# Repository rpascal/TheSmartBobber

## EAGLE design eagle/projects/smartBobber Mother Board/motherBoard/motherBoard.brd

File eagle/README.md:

# Set up Eagle

Once downloaded:
 - options
 - directories
 - Set up paths to what was pulled from git

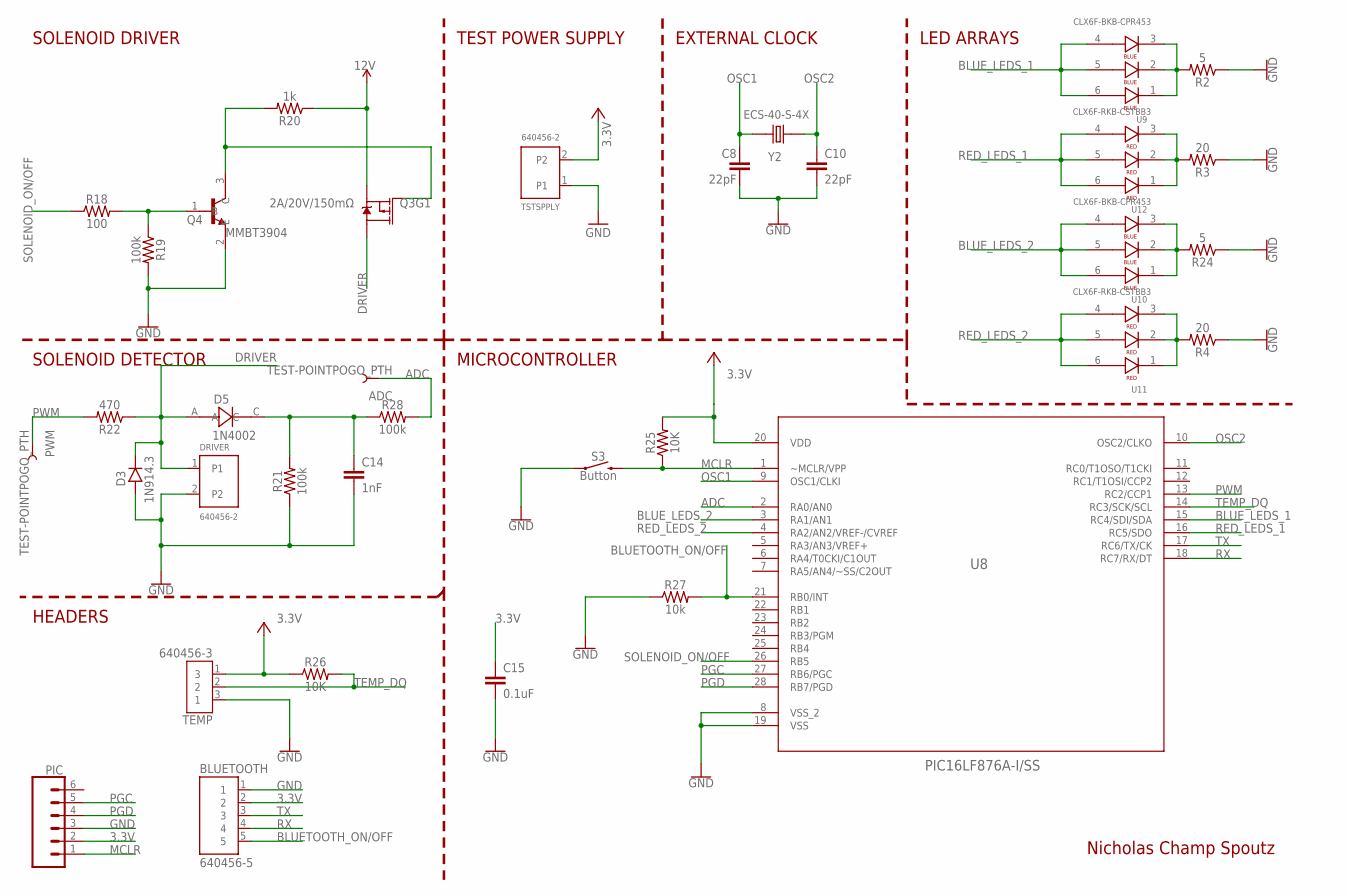
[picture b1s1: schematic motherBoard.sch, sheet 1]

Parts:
ADC: TEST-POINTPOGO_PTH; 1X01_NO_SILK
BLUETOOTH: 640456-5; TE_640456-5
C8, C10: 22pF; 0603
C14: 1nF; 0603
C15: 0.1uF; 0603
D3: 1N914.3; DO35-3
D5: 1N4002; DIOAD520W79L463D238
DRIVER: 640456-2; TE_640456-2
PIC: CONN_06SILK_FEMALE_PTH; 1X06
PWM: TEST-POINTPOGO_PTH; 1X01_NO_SILK
Q3: 2A/20V/150mΩ; SOT26
Q4: MMBT3904; SOT95P240X120-3N
R2, R24: 5; 0603
R3, R4: 20; 0603
R18: 100; 0603
R19, R21, R28: 100k; 0603
R20: 1k; 0603
R22: 470; 0603
R25, R26: 10K; 0603
R27: 10k; 0603
S3: Button; TACTILE_SWITCH_SMD_5.2MM
TEMP: 640456-3; CONN_640456-3
TSTSPPLY: 640456-2; TE_640456-2
U8: PIC16LF876A-I/SS; SOP254P785X200-28N
U9, U10: CLX6F-BKB-CPR453; SOJ100P350X290-6N
U11, U12: CLX6F-RKB-CSTBB3; SOJ100P350X290-6N
Y2: ECS-40-S-4X; XTAL_ECS-40-S-4X

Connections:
3.3V: BLUETOOTH.2, C15.1, PIC.2, R25.2, R26.1, TEMP.1 (3), TSTSPPLY.2, U8.20 (VDD); also elsewhere on the board
12V: Q3.S1 (S), R20.1; also elsewhere on the board
ADC: ADC.1, R28.2, U8.2 (RA0/AN0)
BLUETOOTH_ON/OFF: BLUETOOTH.5, R27.2, U8.21 (RB0/INT)
BLUE_LEDS_1: U8.15 (RC4/SDI/SDA), U9.4, U9.5, U9.6
BLUE_LEDS_2: U8.3 (RA1/AN1), U10.4, U10.5, U10.6
DRIVER: D3.C, D5.A, DRIVER.1, Q3.D1 (D), R22.1
GND: BLUETOOTH.1, C8.2, C10.2, C14.2, C15.2, D3.A, DRIVER.2, PIC.3, Q4.2 (E), R2.1, R3.1, R4.1, R19.2, R21.1, R24.1, R27.1, S3.1, TEMP.3 (1), TSTSPPLY.1, U8.8 (VSS_2), U8.19 (VSS); also elsewhere on the board
MCLR: PIC.1, R25.1, S3.3 (2), U8.1 (~MCLR/VPP)
unnamed: R2.2, U9.1, U9.2, U9.3
unnamed: C14.1, D5.C, R21.2, R28.1
unnamed: R3.2, U12.1, U12.2, U12.3
unnamed: R24.2, U10.1, U10.2, U10.3
unnamed: Q4.1 (B), R18.2, R19.1
unnamed: Q3.G1 (G), Q4.3 (C), R20.2
unnamed: R4.2, U11.1, U11.2, U11.3
OSC1: C8.1, U8.9 (OSC1/CLKI), Y2.1
OSC2: C10.1, U8.10 (OSC2/CLKO), Y2.2
PGC: PIC.5, U8.27 (RB6/PGC)
PGD: PIC.4, U8.28 (RB7/PGD)
PWM: PWM.1, R22.2, U8.13 (RC2/CCP1)
RED_LEDS_1: U8.16 (RC5/SDO), U12.4, U12.5, U12.6
RED_LEDS_2: U8.4 (RA2/AN2/VREF-/CVREF), U11.4, U11.5, U11.6
RX: BLUETOOTH.4, U8.18 (RC7/RX/DT)
SOLENOID_ON/OFF: R18.1, U8.26 (RB5)
TEMP_DQ: R26.2, TEMP.2, U8.14 (RC3/SCK/SCL)
TX: BLUETOOTH.3, U8.17 (RC6/TX/CK)

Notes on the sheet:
SOLENOID DRIVER
SOLENOID DETECTOR
HEADERS
TEST POWER SUPPLY
EXTERNAL CLOCK
LED ARRAYS
MICROCONTROLLER
Nicholas Champ Spoutz

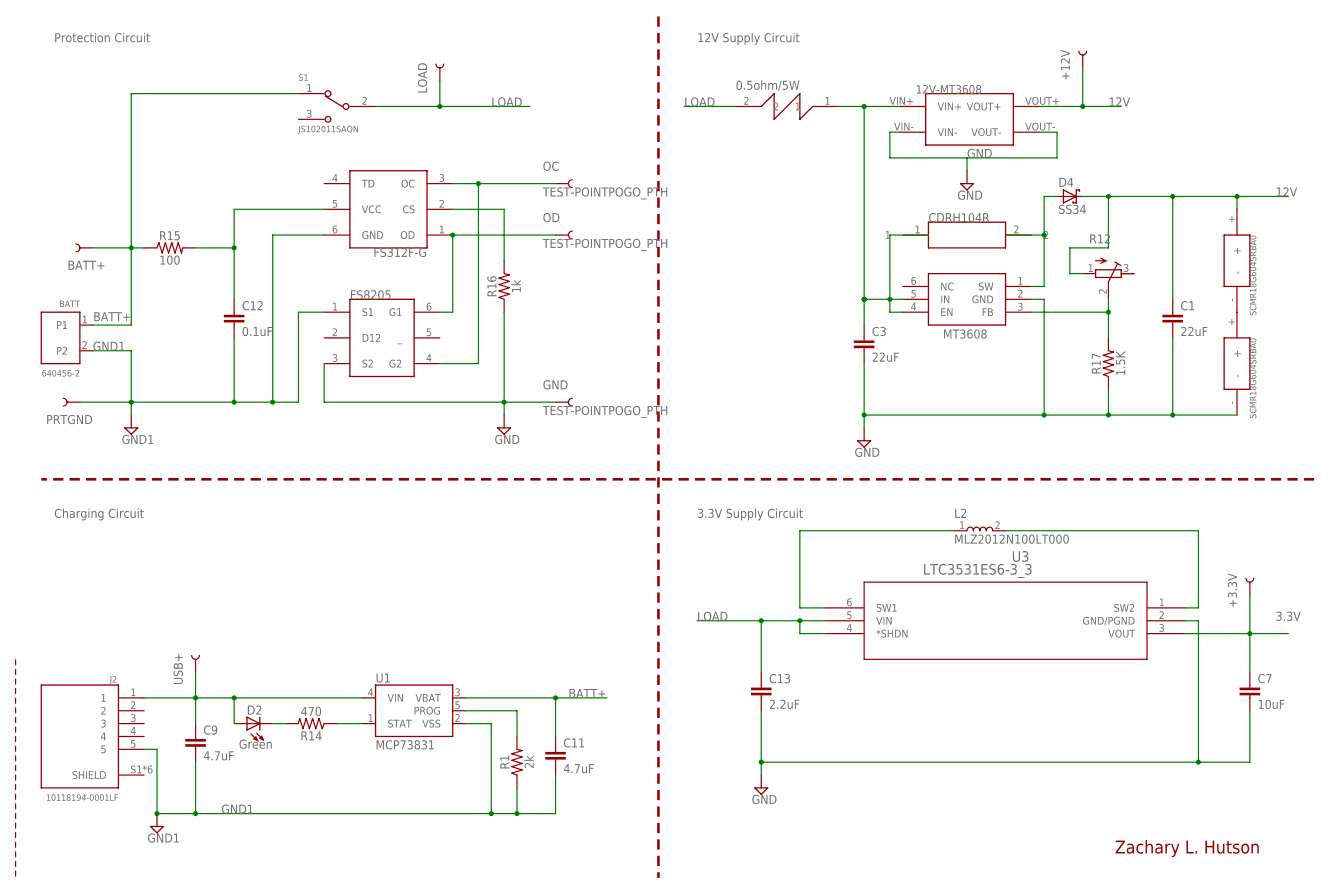
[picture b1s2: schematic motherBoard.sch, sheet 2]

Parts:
+3.3V, +12V: TEST-POINTPOGO_PTH; 1X01_NO_SILK
BATT: 640456-2; TE_640456-2
BATT+: TEST-POINTPOGO_PTH; 1X01_NO_SILK
C1: 22uF; 0805
C3: 22uF; 0603
C7: 10uF; 0603
C9, C11: 4.7uF; 0603
C12: 0.1uF; 0603
C13: 2.2uF; 0603
C16, C17: SCMR18G604SRBA0; SUPERCAP
D2: Green; LED-0603
D4: SS34; SMB
GND: TEST-POINTPOGO_PTH; 1X01_NO_SILK
J2: 10118194-0001LF; AMPHENOL_10118194-0001LF
L1: CDRH104R; 220-INDUCTOR
L2: MLZ2012N100LT000; INDC2012X125
LOAD: TEST-POINTPOGO_PTH; 1X01_NO_SILK
OC: TEST-POINTPOGO_PTH; 1X01_NO_SILK
OD: TEST-POINTPOGO_PTH; 1X01_NO_SILK
PRTGND: TEST-POINTPOGO_PTH; 1X01_NO_SILK
R1: 2k; 0603
R12: R-TRIMM3296P; RTRIM3296P
R14: 470; 0603
R15: 100; 0603
R16: 1k; 0603
R17: 1.5K; 0603
R30: WNER50FET; RESISTOR
S1: JS102011SAQN; SW_JS102011SAQN
U1: MCP73831; SOT23-5
U2: MT3608; SOT95P280X145-6N
U3: LTC3531ES6-3_3; TSOT-23_S6
U$1: 12V-BOARD; PERF_BOARD
U$3: FS312F-G; SOT-23-6
U$4: FS8205; SOT-23-6
USB+: TEST-POINTPOGO_PTH; 1X01_NO_SILK

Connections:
3.3V: +3.3V.1, C7.1, U3.3 (VOUT); also elsewhere on the board
12V: +12V.1, C1.1, C16.+, D4.C, R12.1 (E), U$1.VOUT+; also elsewhere on the board
BATT+: BATT.1, BATT+.1, C11.1, R15.1, S1.1, U1.3 (VBAT)
GND: C1.2, C3.2, C7.2, C13.2, C17.-, GND.1, R16.1, R17.1, U2.2 (GND), U3.2 (GND/PGND), U$1.VIN-, U$1.VOUT-, U$4.3 (S2); also elsewhere on the board
GND1: BATT.2, C9.2, C11.2, C12.2, J2.5, PRTGND.1, R1.1, U1.2 (VSS), U$3.6 (GND), U$4.1 (S1)
LOAD: C13.1, LOAD.1, R30.2, S1.2, U3.4 (*SHDN), U3.5 (VIN)
unnamed: D2.C, R14.2
unnamed: C3.1, L1.1, R30.1, U2.4 (EN), U2.5 (IN), U$1.VIN+
unnamed: R14.1, U1.1 (STAT)
unnamed: R1.2, U1.5 (PROG)
unnamed: R16.2, U$3.2 (CS)
unnamed: C9.1, D2.A, J2.1, U1.4 (VIN), USB+.1
unnamed: D4.A, L1.2, U2.1 (SW)
unnamed: R12.2 (S), R17.2, U2.3 (FB)
unnamed: L2.1, U3.6 (SW1)
unnamed: L2.2, U3.1 (SW2)
unnamed: OD.1, U$3.1 (OD), U$4.6 (G1)
unnamed: OC.1, U$3.3 (OC), U$4.4 (G2)
unnamed: C16.-, C17.+
unnamed: C12.1, R15.2, U$3.5 (VCC)

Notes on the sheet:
Charging Circuit
Protection Circuit
3.3V Supply Circuit
12V Supply Circuit
Zachary L. Hutson

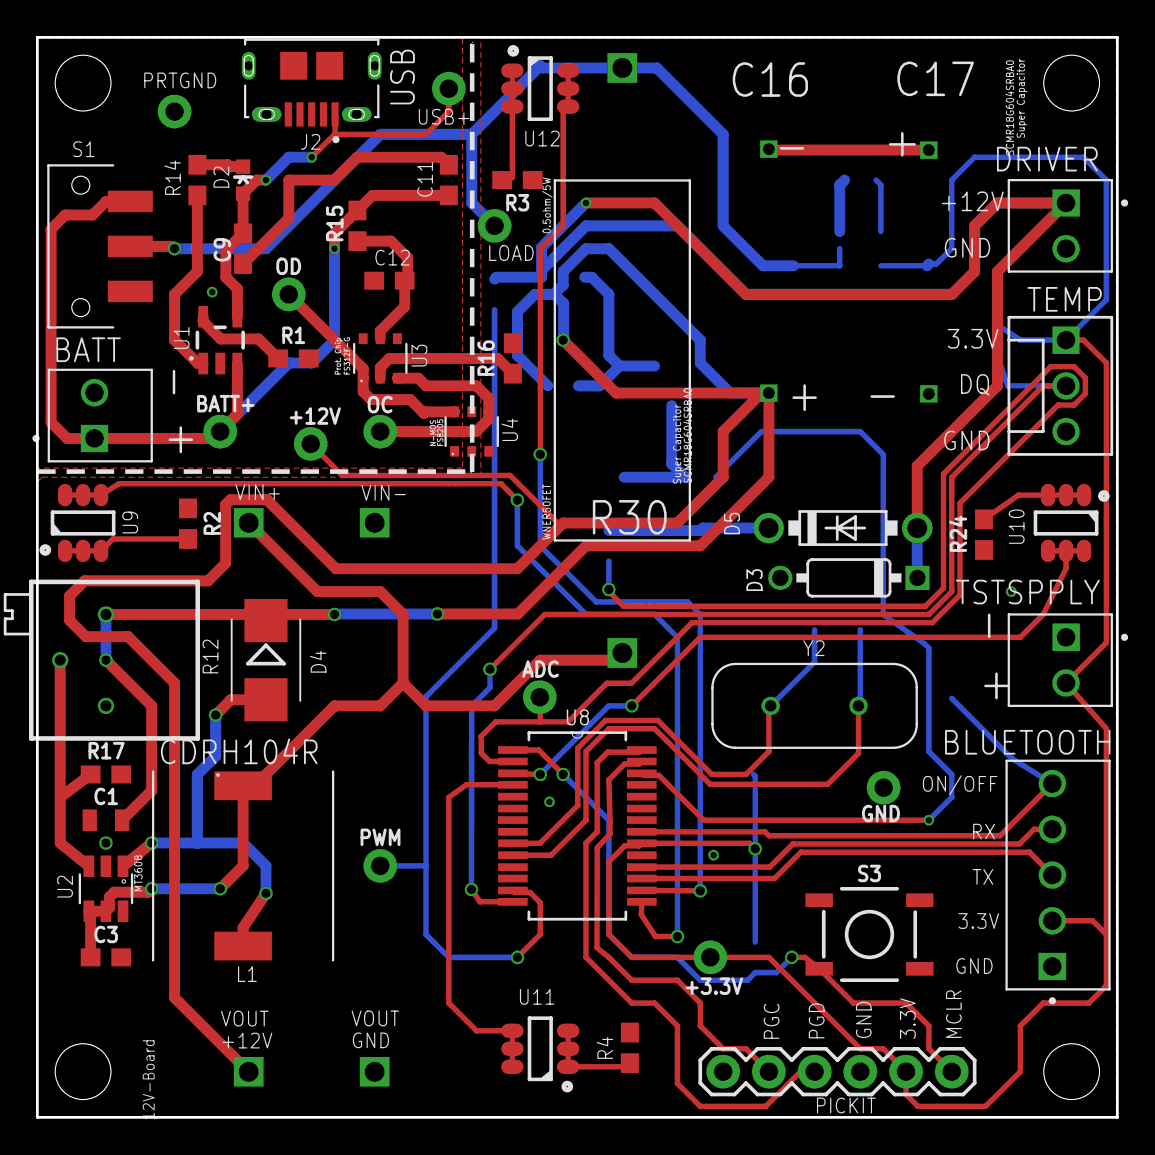
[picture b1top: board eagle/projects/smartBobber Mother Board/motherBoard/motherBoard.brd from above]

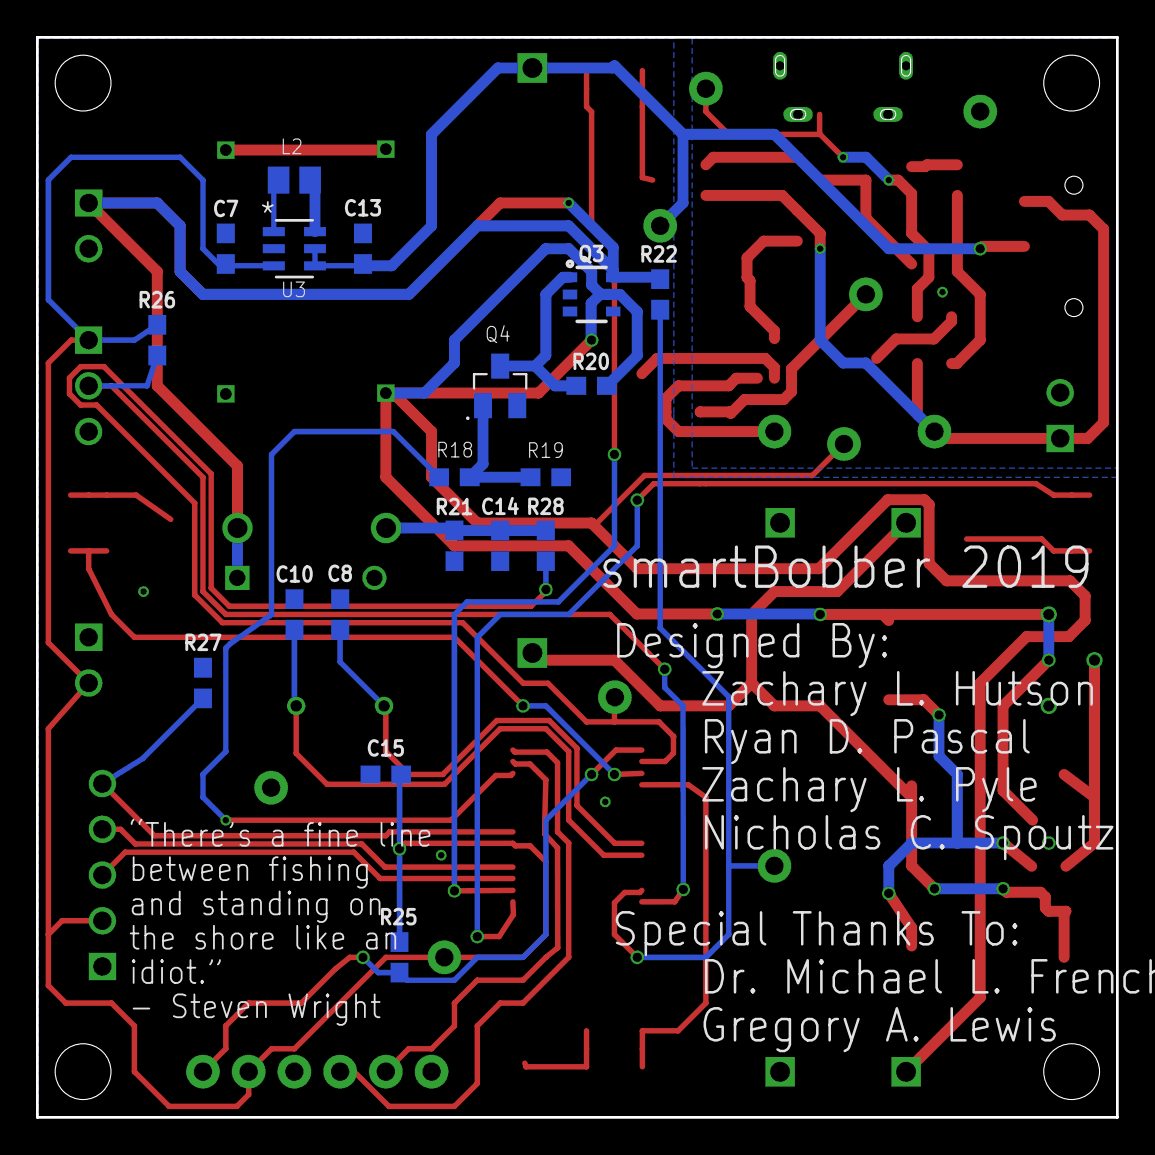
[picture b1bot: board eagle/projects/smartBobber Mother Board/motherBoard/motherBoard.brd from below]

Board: 2 copper layers, 60.0 x 60.0 mm, 73 parts (19 on the bottom side), 44 nets.

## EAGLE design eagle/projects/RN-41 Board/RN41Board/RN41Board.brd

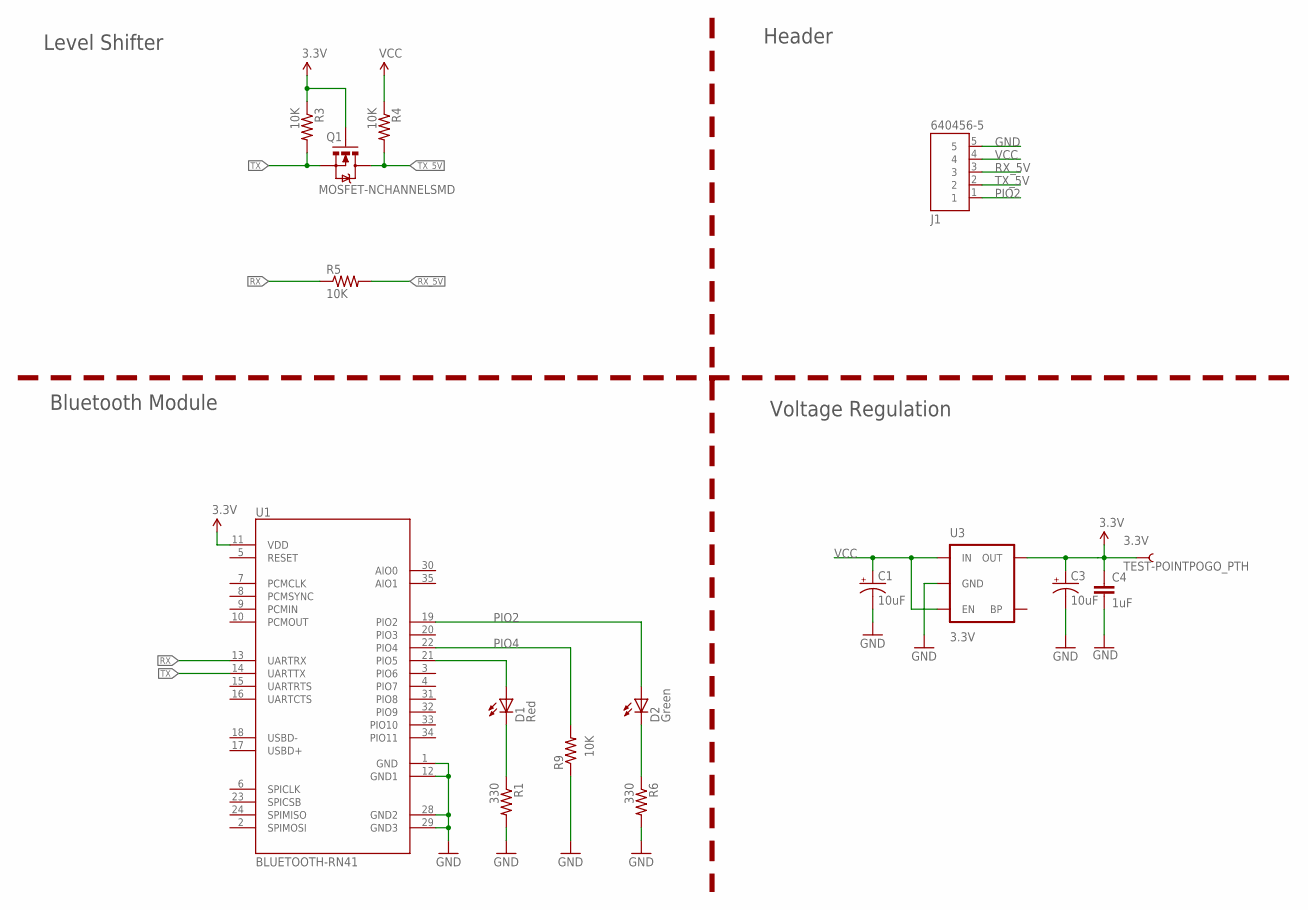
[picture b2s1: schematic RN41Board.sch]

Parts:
3.3V: TEST-POINTPOGO_PTH; 1X01_NO_SILK
C1, C3: 10uF; EIA3216
C4: 1uF; 0603-CAP
D1: Red; LED-0603
D2: Green; LED-0603
J1: 640456-5; TE_640456-5
Q1: MOSFET-NCHANNELSMD; SOT23-3
R1, R6: 330; 0603-RES
R3, R4, R5, R9: 10K; 0603-RES
U1: BLUETOOTH-RN41; RN41
U3: 3.3V; SOT23-5

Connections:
3.3V: 3.3V.1, C3.A (+), C4.1, Q1.1 (G), R3.1, U1.11 (VDD), U3.5 (OUT)
D1: D1.C, R1.1
D2: D2.C, R6.1
GND: C1.C (-), C3.C (-), C4.2, J1.5, R1.2, R6.2, R9.1, U1.1 (GND), U1.12 (GND1), U1.28 (GND2), U1.29 (GND3), U3.2 (GND)
unnamed: D1.A, U1.21 (PIO5)
PIO2: D2.A, J1.1, U1.19 (PIO2)
PIO4: R9.2, U1.22 (PIO4)
RX: R5.1, U1.13 (UARTRX)
RX_5V: J1.3, R5.2
TX: Q1.2 (S), R3.2, U1.14 (UARTTX)
TX_5V: J1.2, Q1.3 (D), R4.2
VCC: C1.A (+), J1.4, R4.1, U3.1 (IN), U3.3 (EN)

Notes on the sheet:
Level Shifter
Header
Voltage Regulation
Bluetooth Module

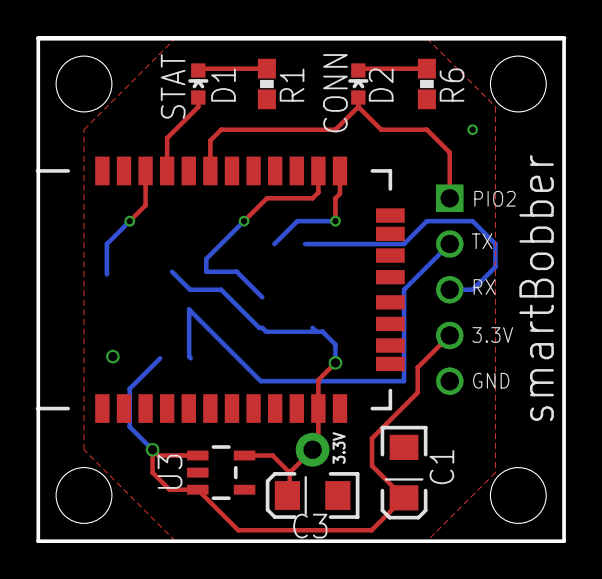
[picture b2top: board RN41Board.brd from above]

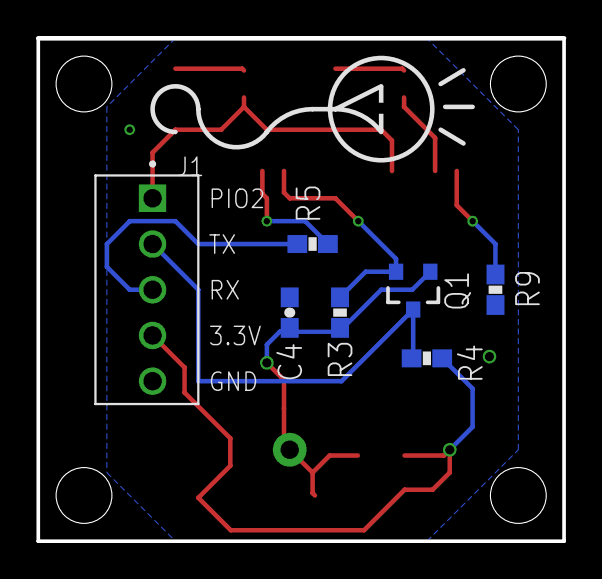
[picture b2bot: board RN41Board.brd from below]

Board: 2 copper layers, 29.2 x 27.9 mm, 16 parts (7 on the bottom side), 12 nets.

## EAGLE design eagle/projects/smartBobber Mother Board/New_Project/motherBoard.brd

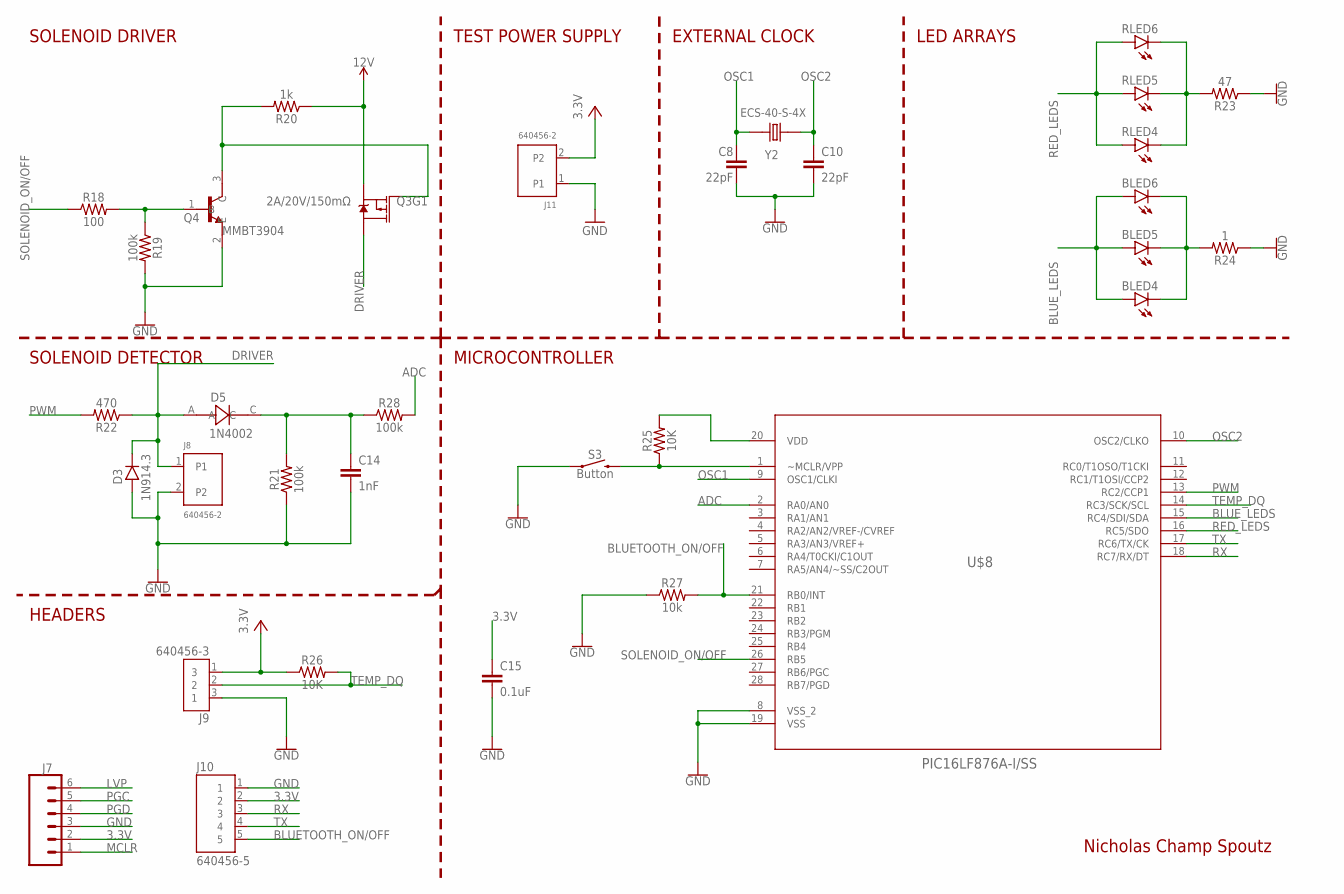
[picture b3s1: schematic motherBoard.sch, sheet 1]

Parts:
BLED4, BLED5, BLED6: LED5MM
C8, C10: 22pF; 0603
C14: 1nF; 0603
C15: 0.1uF; 0603
D3: 1N914.3; DO35-3
D5: 1N4002; DIOAD520W79L463D238
J7: CONN_06SILK_FEMALE_PTH; 1X06
J8, J11: 640456-2; TE_640456-2
J9: 640456-3; CONN_640456-3
J10: 640456-5; TE_640456-5
Q3: 2A/20V/150mΩ; SOT26
Q4: MMBT3904; SOT95P240X120-3N
R18: 100; 0603
R19, R21, R28: 100k; 0603
R20: 1k; 0603
R22: 470; 0603
R23: 47; 0603
R24: 1; 0603
R25, R26: 10K; 0603
R27: 10k; 0603
RLED4, RLED5, RLED6: LED5MM
S3: Button; TACTILE_SWITCH_SMD_5.2MM
U$8: PIC16LF876A-I/SS; SOP254P785X200-28N
Y2: ECS-40-S-4X; XTAL_ECS-40-S-4X

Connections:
3.3V: C15.1, J7.2, J10.2, R25.2, U$8.20 (VDD); also elsewhere on the board
ADC: C14.1, D5.C, R21.2, R28.1, R28.2, U$8.2 (RA0/AN0)
BLUETOOTH_ON/OFF: J10.5, R27.2, U$8.21 (RB0/INT)
BLUE_LEDS: BLED4.A, BLED5.A, BLED6.A, U$8.15 (RC4/SDI/SDA)
DRIVER: D3.C, D5.A, J8.1, Q3.D1 (D), R22.1
GND: C8.2, C10.2, C14.2, C15.2, D3.A, J7.3, J8.2, J9.3 (1), J10.1, J11.1, Q4.2 (E), R19.2, R21.1, R23.1, R24.1, R27.1, S3.1, U$8.8 (VSS_2), U$8.19 (VSS)
LVP: J7.6
MCLR: J7.1
unnamed: Q4.1 (B), R18.2, R19.1
unnamed: Q3.G1 (G), Q4.3 (C), R20.2
unnamed: BLED4.K (C), BLED5.K (C), BLED6.K (C), R24.2
unnamed: R23.2, RLED4.K (C), RLED5.K (C), RLED6.K (C)
unnamed: R25.1, S3.3 (2), U$8.1 (~MCLR/VPP)
OSC1: C8.1, U$8.9 (OSC1/CLKI), Y2.1
OSC2: C10.1, U$8.10 (OSC2/CLKO), Y2.2
PGC: J7.5
PGD: J7.4
PWM: R22.2, U$8.13 (RC2/CCP1)
RED_LEDS: RLED4.A, RLED5.A, RLED6.A, U$8.16 (RC5/SDO)
RX: J10.3, U$8.18 (RC7/RX/DT)
SOLENOID_ON/OFF: R18.1, U$8.26 (RB5)
TEMP_DQ: J9.2, R26.2, U$8.14 (RC3/SCK/SCL)
TX: J10.4, U$8.17 (RC6/TX/CK)
VCC: J9.1 (3), J11.2, Q3.S1 (S), R20.1, R26.1

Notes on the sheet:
SOLENOID DRIVER
SOLENOID DETECTOR
HEADERS
TEST POWER SUPPLY
EXTERNAL CLOCK
LED ARRAYS
MICROCONTROLLER
Nicholas Champ Spoutz

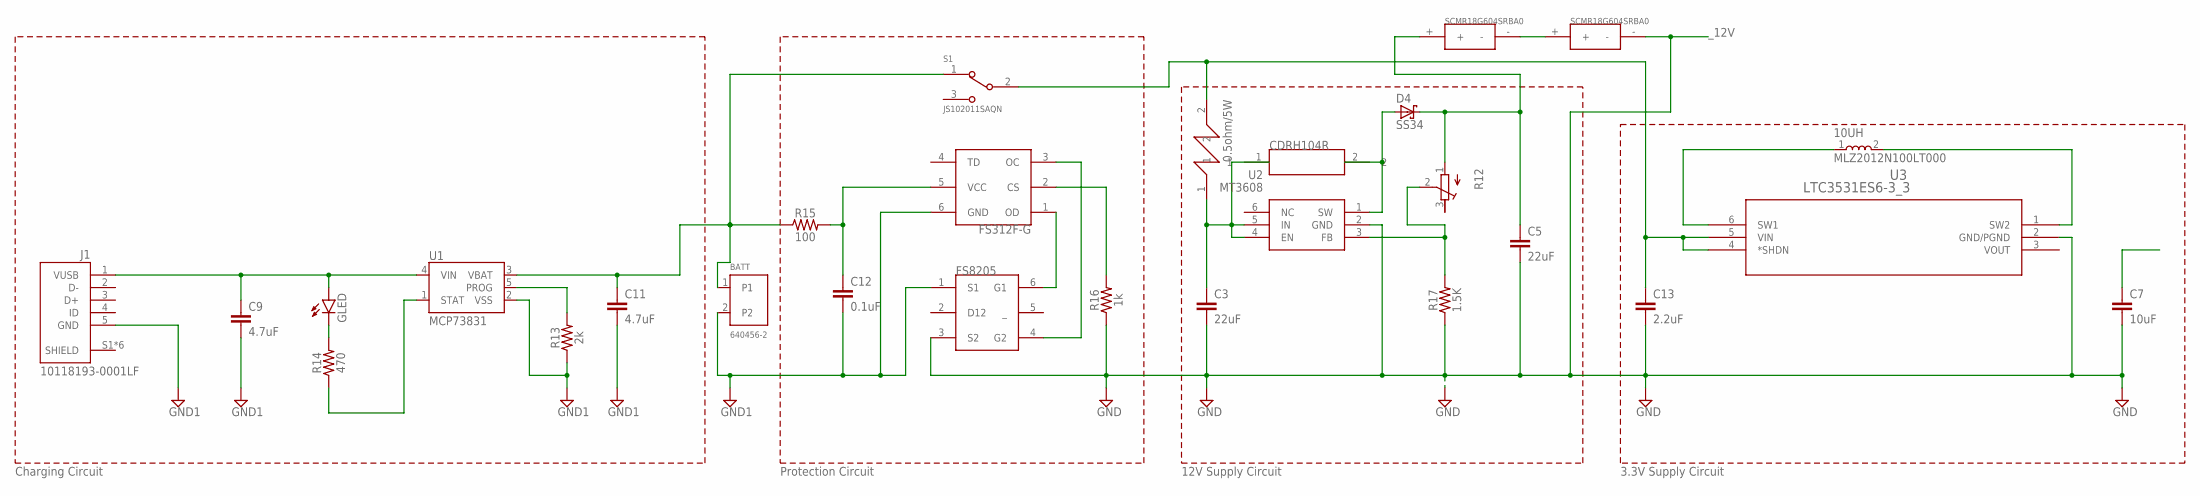
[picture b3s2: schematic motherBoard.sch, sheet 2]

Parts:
10UH: MLZ2012N100LT000; INDC2012X125
BATT: 640456-2; TE_640456-2
C3, C5: 22uF; 0603
C7: 10uF; 0603
C9, C11: 4.7uF; 0603
C12: 0.1uF; 0603
C13: 2.2uF; 0603
D4: SS34; SMB
GLED: LED5MM
J1: 10118193-0001LF; FCI_10118193-0001LF
R12: R-TRIMM3296P; RTRIM3296P
R13: 2k; 0805
R14: 470; 0603
R15: 100; 0603
R16: 1k; 0603
R17: 1.5K; 0603
S1: JS102011SAQN; SW_JS102011SAQN
U1: MCP73831; SOT23-5
U2: MT3608; SOT95P280X145-6N
U3: LTC3531ES6-3_3; TSOT-23_S6
U$2: CDRH104R; 220-INDUCTOR
U$3: FS312F-G; SOT-23-6
U$4: FS8205; SOT-23-6
U$5, U$6: SCMR18G604SRBA0; SUPERCAP
U$7: WNER50FET; RESISTOR

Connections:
3.3V: C7.1; also elsewhere on the board
12V: C5.1, D4.C, R12.1 (E), U$5.+
unnamed: GLED.K (C), R14.2
unnamed: R14.1, U1.1 (STAT)
unnamed: BATT.1, C11.1, R15.1, S1.1, U1.3 (VBAT)
unnamed: R13.2, U1.5 (PROG)
unnamed: R16.2, U$3.2 (CS)
unnamed: C9.1, GLED.A, J1.1 (VUSB), U1.4 (VIN)
unnamed: D4.A, U2.1 (SW), U$2.2
unnamed: R12.2 (S), R17.2, U2.3 (FB)
unnamed: 10UH.1, U3.6 (SW1)
unnamed: 10UH.2, U3.1 (SW2)
unnamed: C13.1, S1.2, U3.4 (*SHDN), U3.5 (VIN), U$7.2
unnamed: U$3.1 (OD), U$4.6 (G1)
unnamed: U$3.3 (OC), U$4.4 (G2)
unnamed: U$5.-, U$6.+
unnamed: C12.1, R15.2, U$3.5 (VCC)
unnamed: C3.1, U2.4 (EN), U2.5 (IN), U$2.1, U$7.1
_12V: BATT.2, C3.2, C5.2, C7.2, C9.2, C11.2, C12.2, C13.2, J1.5 (GND), R13.1, R16.1, R17.1, U1.2 (VSS), U2.2 (GND), U3.2 (GND/PGND), U$3.6 (GND), U$4.1 (S1), U$4.3 (S2), U$6.-

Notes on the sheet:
Charging Circuit
Protection Circuit
3.3V Supply Circuit
12V Supply Circuit

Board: 2 copper layers, 61 parts (0 on the bottom side), 38 nets, no tracks yet.

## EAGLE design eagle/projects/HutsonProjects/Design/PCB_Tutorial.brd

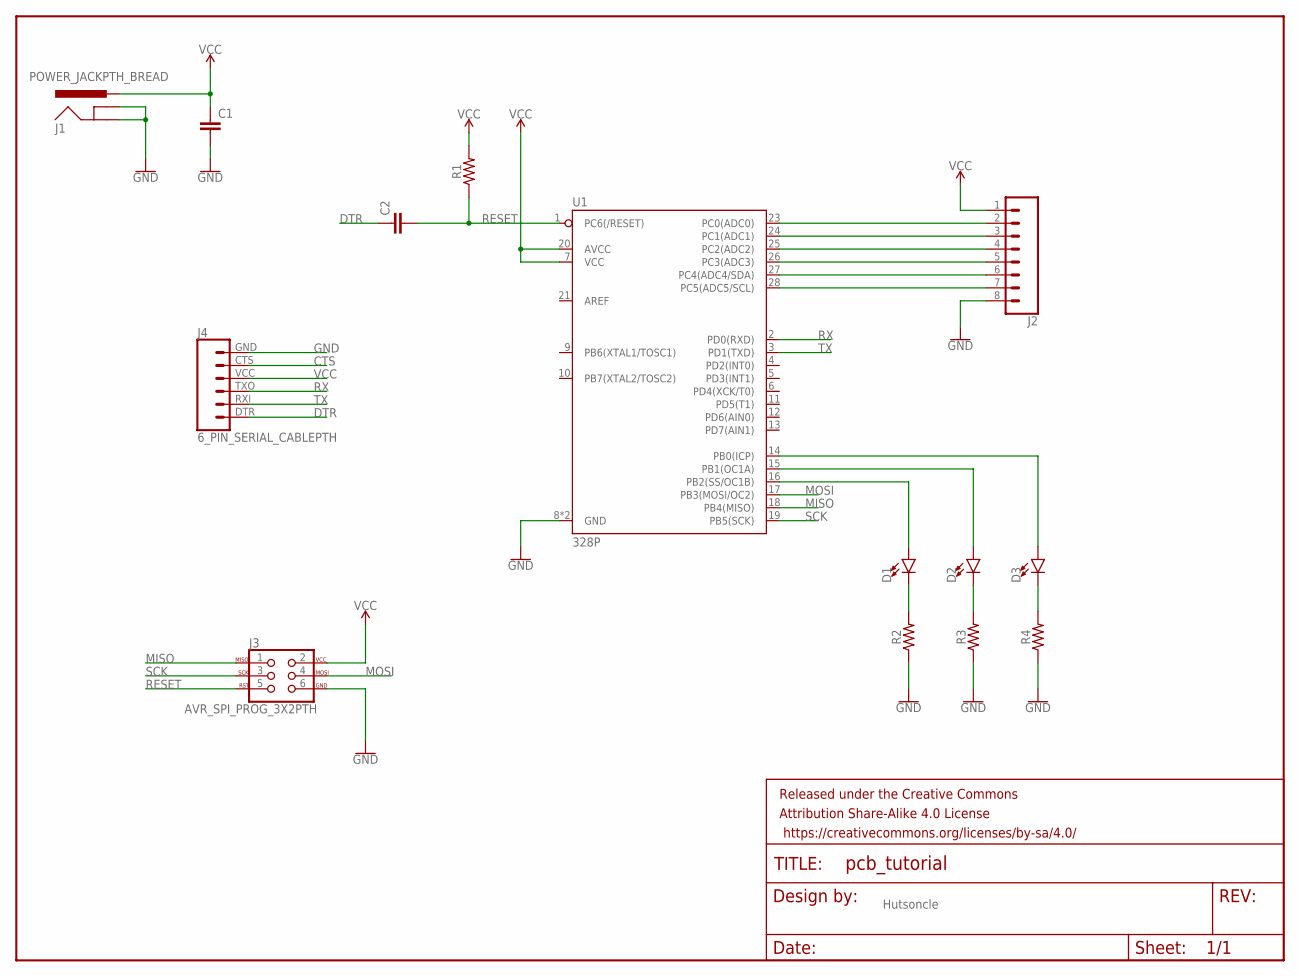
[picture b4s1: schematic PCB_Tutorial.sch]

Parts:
C1, C2: 0.1uF; CAP-PTH-SMALL-KIT
D1, D2, D3: LED5MM; LED_5MM
FRAME1: FRAME-LETTER; CREATIVE_COMMONS
J1: POWER_JACKPTH_BREAD; POWER_JACK_PTH_BREAD
J2: CONN_08"; 1X08
J3: AVR_SPI_PROG_3X2PTH; 2X3
J4: 6_PIN_SERIAL_CABLEPTH; FTDI_BASIC
R1, R2, R3, R4: AXIAL-0.3
U1: 328P; DIP28

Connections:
CTS: J4.CTS (5)
DTR: C2.1, J4.DTR (1)
GND: C1.2, J1.GND, J1.GNDBREAK, J2.8, J3.6, J4.GND (6), R2.P$1 (1), R3.P$1 (1), R4.P$1 (1), U1.8 (GND), U1.22 (GND)
MISO: J3.1, U1.18 (PB4(MISO))
MOSI: J3.4, U1.17 (PB3(MOSI/OC2))
unnamed: J2.2, U1.23 (PC0(ADC0))
unnamed: J2.3, U1.24 (PC1(ADC1))
unnamed: J2.4, U1.25 (PC2(ADC2))
unnamed: J2.5, U1.26 (PC3(ADC3))
unnamed: J2.6, U1.27 (PC4(ADC4/SDA))
unnamed: J2.7, U1.28 (PC5(ADC5/SCL))
unnamed: D1.K (C), R2.P$2 (2)
unnamed: D2.K (C), R3.P$2 (2)
unnamed: D3.K (C), R4.P$2 (2)
unnamed: D3.A, U1.14 (PB0(ICP))
unnamed: D2.A, U1.15 (PB1(OC1A))
unnamed: D1.A, U1.16 (PB2(SS/OC1B))
RESET: C2.2, J3.5, R1.P$1 (1), U1.1 (PC6(/RESET))
RX: J4.TXO (3), U1.2 (PD0(RXD))
SCK: J3.3, U1.19 (PB5(SCK))
TX: J4.RXI (2), U1.3 (PD1(TXD))
VCC: C1.1, J1.PWR, J2.1, J3.2, J4.VCC (4), R1.P$2 (2), U1.7 (VCC), U1.20 (AVCC)

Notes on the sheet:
Hutsoncle

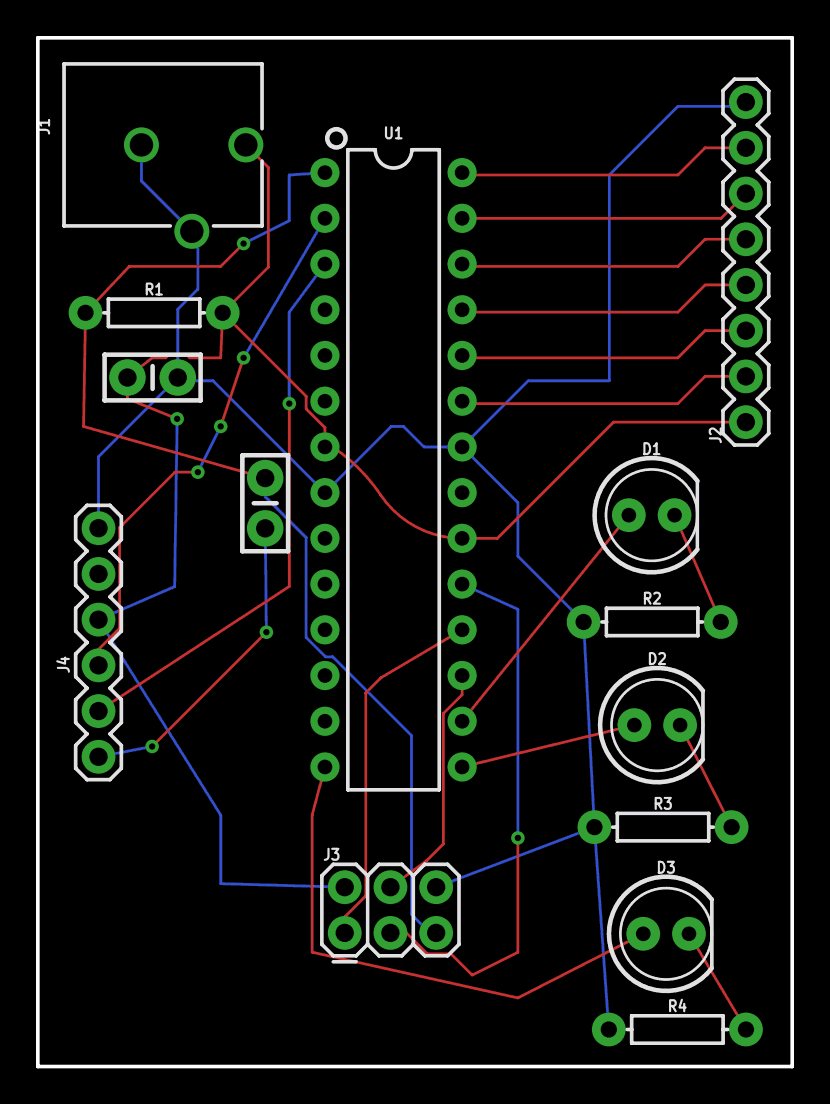
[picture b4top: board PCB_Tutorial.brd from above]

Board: 2 copper layers, 41.9 x 57.2 mm, 15 parts (0 on the bottom side), 21 nets.

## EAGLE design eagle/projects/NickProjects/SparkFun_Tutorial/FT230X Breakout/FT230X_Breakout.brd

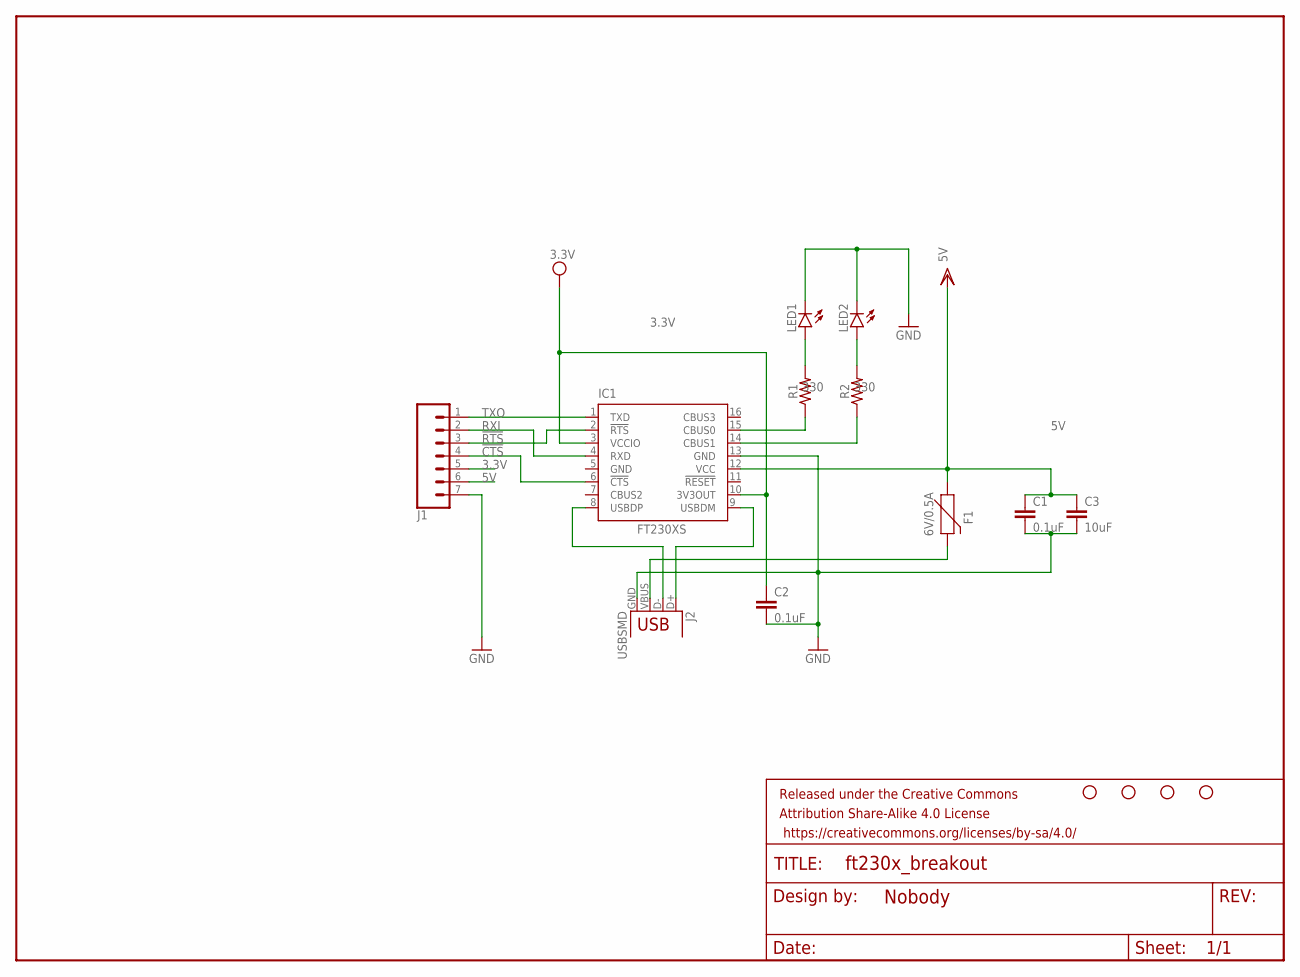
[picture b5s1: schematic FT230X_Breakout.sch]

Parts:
C1, C2: 0.1uF; C0603
C3: 10uF; C1206
F1: 6V/0.5A; 1206
FRAME1: FRAME-LETTERNO_PACKAGE; DUMMY
H1, H2, H3, H4: STAND-OFF
IC1: FT230XS; SSOP16
J1: CONN_07; 1X07
J2: USBSMD; USB-MINIB
LED1, LED2: LEDCHIP-LED0603; CHIP-LED0603
R1, R2: 330; 0603

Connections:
3.3V: C2.1, IC1.3 (VCCIO), IC1.10 (3V3OUT), J1.5
5V: C1.1, C3.1, F1.1, IC1.12 (VCC), J1.6
!CTS: IC1.6 (!CTS), J1.4
!RTS: IC1.2 (!RTS), J1.3
GND: C1.2, C2.2, C3.2, IC1.5 (GND), IC1.13 (GND), J1.7, J2.GND, LED1.C, LED2.C
unnamed: IC1.9 (USBDM), J2.D+
unnamed: IC1.8 (USBDP), J2.D-
unnamed: F1.2, J2.VBUS
unnamed: IC1.15 (CBUS0), R1.1
unnamed: IC1.14 (CBUS1), R2.1
unnamed: LED1.A, R1.2
unnamed: LED2.A, R2.2
RXI: IC1.4 (RXD), J1.2
TXO: IC1.1 (TXD), J1.1

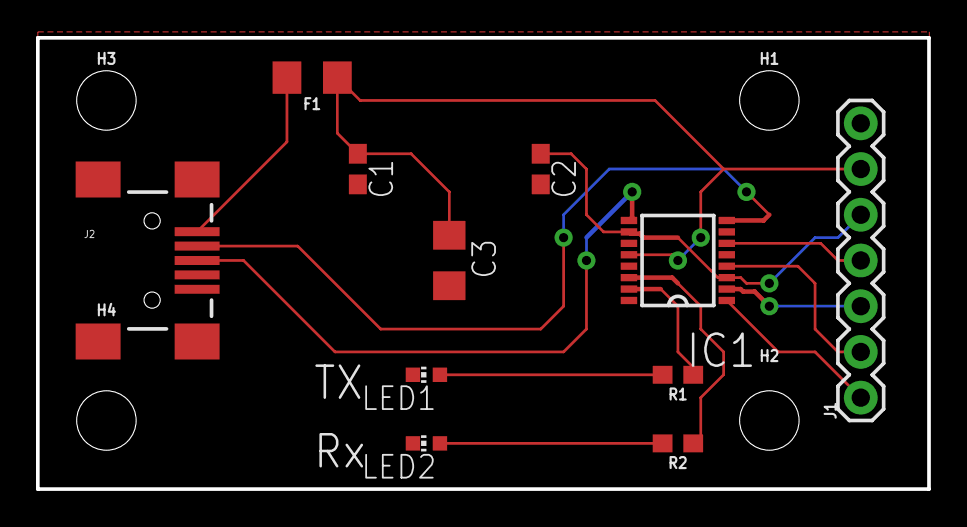
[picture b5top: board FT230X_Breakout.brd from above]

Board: 2 copper layers, 49.5 x 25.1 mm, 16 parts (0 on the bottom side), 14 nets.

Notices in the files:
parts and their libraries:
SparkFun-Resistors: Licensing: Creative Commons ShareAlike 4.0 International - https://creativecommons.org/licenses/by-sa/4.0
SparkFun-Aesthetics: Released under the Creative Commons Attribution Share-Alike 4.0 License
SparkFun-Aesthetics: https://creativecommons.org/licenses/by-sa/4.0
